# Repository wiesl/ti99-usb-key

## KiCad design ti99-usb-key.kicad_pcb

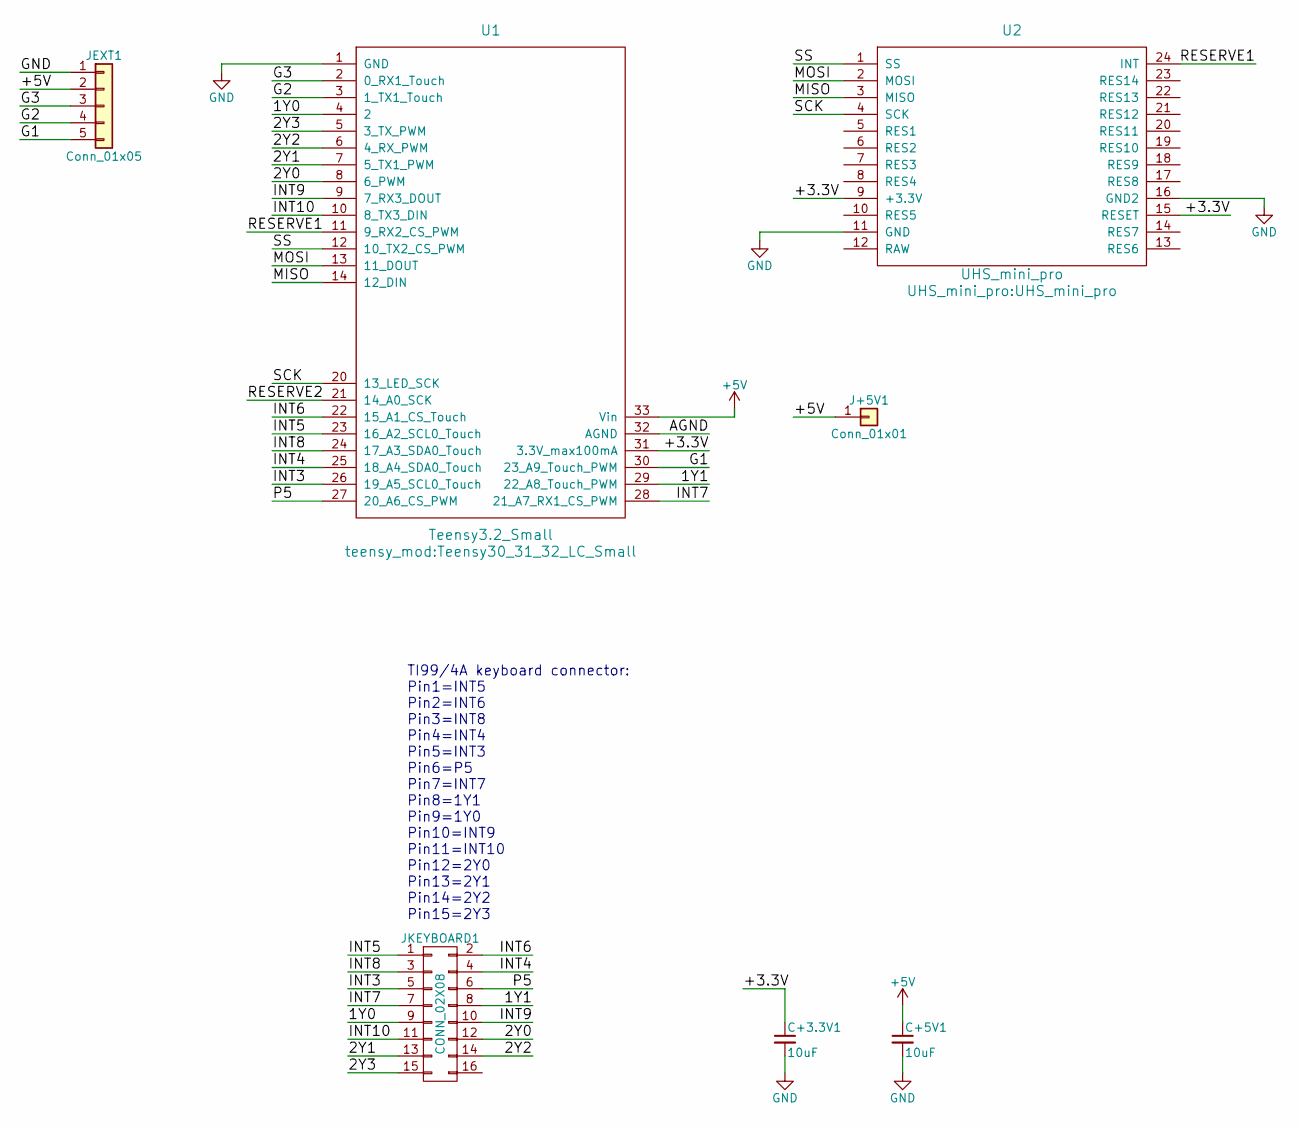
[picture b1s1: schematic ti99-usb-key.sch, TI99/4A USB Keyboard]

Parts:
C+3.3V1, C+5V1: 10uF; CP_Radial_D5.0mm_P2.50mm
J+5V1: Conn_01x01; SL-101-X-XX_1x01
JEXT1: Conn_01x05; SL-105-X-XX_1x05
JKEYBOARD1: CONN_02X08; IDC_Header_Straight_16pins
U1: Teensy3.2_Small; Teensy30_31_32_LC_Small
U2: UHS_mini_pro

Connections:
+5V: C+5V1.1, J+5V1.1, JEXT1.2, U1.33 (Vin)
/1Y0: JKEYBOARD1.9, U1.4 (2)
/1Y1: JKEYBOARD1.8, U1.29 (22_A8_Touch_PWM)
/2Y0: JKEYBOARD1.12, U1.8 (6_PWM)
/2Y1: JKEYBOARD1.13, U1.7 (5_TX1_PWM)
/2Y2: JKEYBOARD1.14, U1.6 (4_RX_PWM)
/2Y3: JKEYBOARD1.15, U1.5 (3_TX_PWM)
/+3.3V: C+3.3V1.1, U1.31 (3.3V_max100mA), U2.9 (+3.3V), U2.15 (RESET)
/AGND: U1.32 (AGND)
/G1: JEXT1.5, U1.30 (23_A9_Touch_PWM)
/G2: JEXT1.4, U1.3 (1_TX1_Touch)
/G3: JEXT1.3, U1.2 (0_RX1_Touch)
/INT3: JKEYBOARD1.5, U1.26 (19_A5_SCL0_Touch)
/INT4: JKEYBOARD1.4, U1.25 (18_A4_SDA0_Touch)
/INT5: JKEYBOARD1.1, U1.23 (16_A2_SCL0_Touch)
/INT6: JKEYBOARD1.2, U1.22 (15_A1_CS_Touch)
/INT7: JKEYBOARD1.7, U1.28 (21_A7_RX1_CS_PWM)
/INT8: JKEYBOARD1.3, U1.24 (17_A3_SDA0_Touch)
/INT9: JKEYBOARD1.10, U1.9 (7_RX3_DOUT)
/INT10: JKEYBOARD1.11, U1.10 (8_TX3_DIN)
/MISO: U1.14 (12_DIN), U2.3 (MISO)
/MOSI: U1.13 (11_DOUT), U2.2 (MOSI)
/P5: JKEYBOARD1.6, U1.27 (20_A6_CS_PWM)
/RESERVE1: U1.11 (9_RX2_CS_PWM), U2.24 (INT)
/RESERVE2: U1.21 (14_A0_SCK)
/SCK: U1.20 (13_LED_SCK), U2.4 (SCK)
/SS: U1.12 (10_TX2_CS_PWM), U2.1 (SS)
GND: C+3.3V1.2, C+5V1.2, JEXT1.1, U1.1 (GND), U2.11 (GND), U2.16 (GND2)

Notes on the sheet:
TI99/4A keyboard connector: Pin1=INT5 Pin2=INT6 Pin3=INT8 Pin4=INT4 Pin5=INT3 Pin6=P5 Pin7=INT7 Pin8=1Y1 Pin9=1Y0 Pin10=INT9 Pin11=INT10 Pin12=2Y0 Pin13=2Y1 Pin14=2Y2 Pin15=2Y3

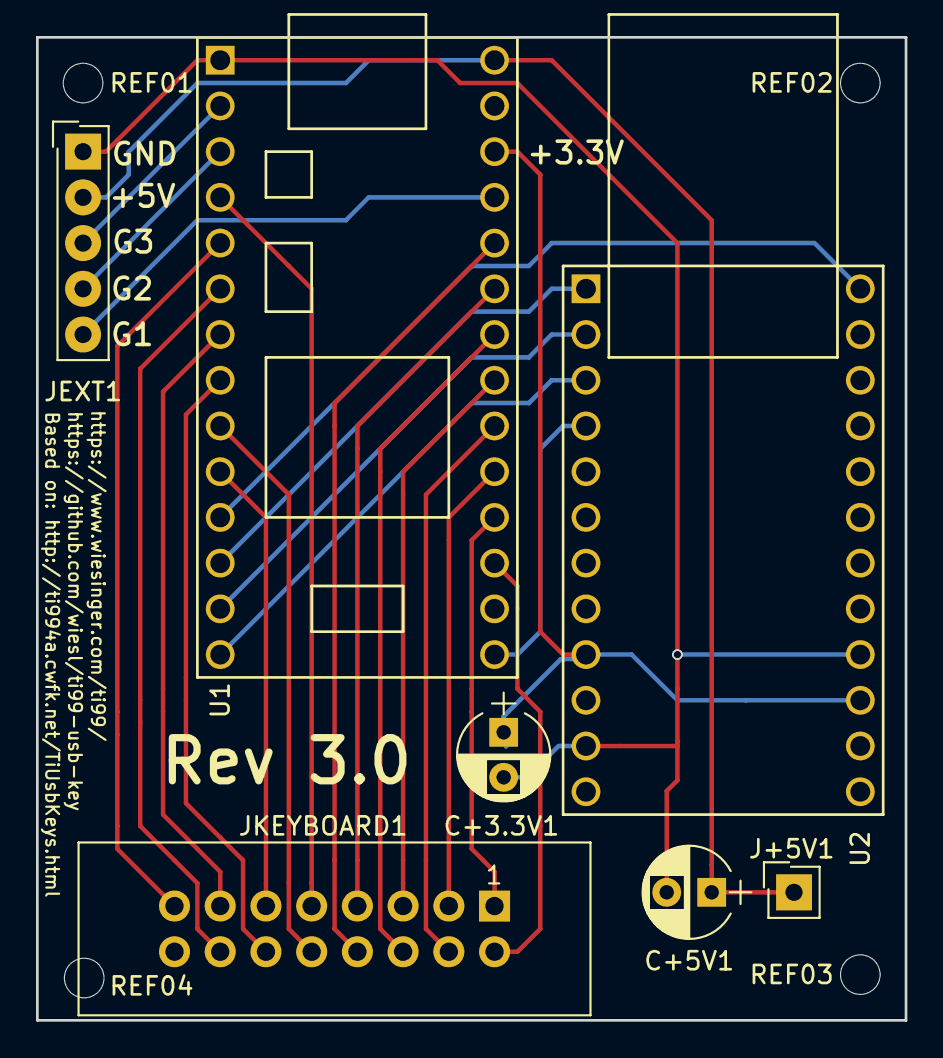
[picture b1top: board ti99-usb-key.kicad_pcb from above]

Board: 2 copper layers, 48.3 x 54.6 mm, 11 parts (0 on the bottom side), 26 nets.

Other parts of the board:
REF01, REF02, REF03, REF04: MountingHole_2.2mm_M2

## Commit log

2017-09-25 initial import, V3.0
